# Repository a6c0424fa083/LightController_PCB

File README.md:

# LightController_PCB
This is the PCB (designed in KiCad) used in the LightController software

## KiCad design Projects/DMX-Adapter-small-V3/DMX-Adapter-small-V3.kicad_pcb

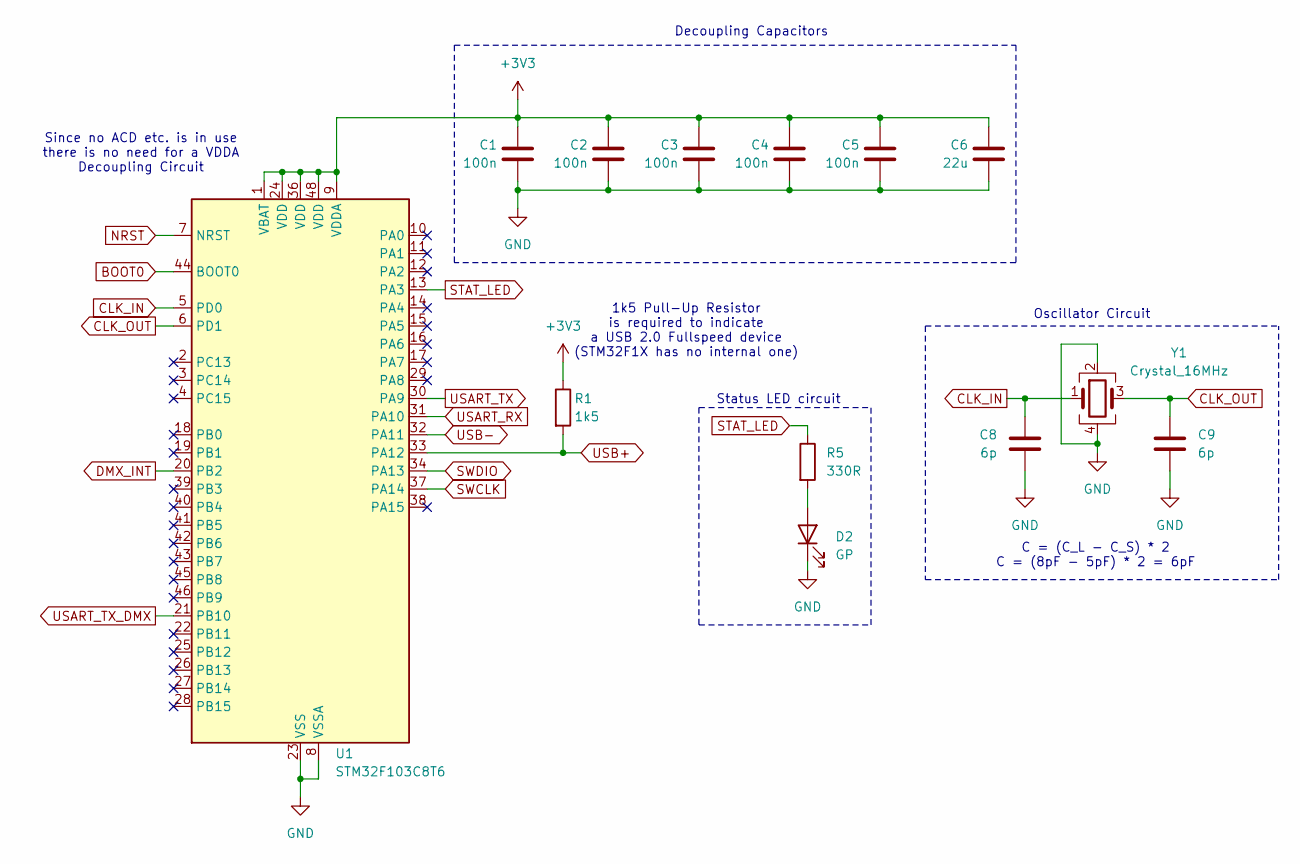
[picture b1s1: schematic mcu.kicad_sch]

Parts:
C1, C2, C3, C4, C5: 100n; C_0402_1005Metric; Mouser-Nr 81-GRM152D70G104ME5D
C6: 22u; C_0603_1608Metric; Mouser-Nr 81-GRM188C80J226ME5D
C8, C9: 6p; C_0402_1005Metric; Mouser-Nr 81-GCQ1555C1H6R0BB1D
D2: GP; D_0603_1608Metric; Mouser-Nr 755-SML-D12V8WT86
R1: 1k5; R_0402_1005Metric; Mouser-Nr 667-ERA-2VEB1501X
R5: 330R; R_0402_1005Metric; Mouser-Nr 71-CRCW0402330RFKEDH
U1: STM32F103C8T6; LQFP-48_7x7mm_P0.5mm; Mouser-Nr 511-STM32F103C8T6
Y1: Crystal_16MHz; Crystal_Wuerth_830108207109; Mouser-Nr 710-830108207109

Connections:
+3V3: C1.1, C2.1, C3.1, C4.1, C5.1, C6.1, R1.1, U1.1 (VBAT), U1.9 (VDDA), U1.24 (VDD), U1.36 (VDD), U1.48 (VDD); also elsewhere on the board
BOOT0: U1.44 (BOOT0); also elsewhere on the board
CLK_IN: C8.1, U1.5 (PD0), Y1.1
CLK_OUT: C9.1, U1.6 (PD1), Y1.3
DMX_INT: U1.20 (PB2); also elsewhere on the board
GND: C1.2, C2.2, C3.2, C4.2, C5.2, C6.2, C8.2, C9.2, D2.1 (K), U1.8 (VSSA), U1.23 (VSS), U1.35 (VSS), U1.47 (VSS), Y1.2, Y1.4; also elsewhere on the board
NRST: U1.7 (NRST); also elsewhere on the board
unnamed: D2.2 (A), R5.2
STAT_LED: R5.1, U1.13 (PA3)
SWCLK: U1.37 (PA14); also elsewhere on the board
SWDIO: U1.34 (PA13); also elsewhere on the board
USART_RX: U1.31 (PA10); also elsewhere on the board
USART_TX: U1.30 (PA9); also elsewhere on the board
USART_TX_DMX: U1.21 (PB10); also elsewhere on the board
USB+: R1.2, U1.33 (PA12); also elsewhere on the board
USB-: U1.32 (PA11); also elsewhere on the board

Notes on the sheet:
Status LED circuit
1k5 Pull-Up Resistor is required to indicate a USB 2.0 Fullspeed device (STM32F1X has no internal one)
Oscillator Circuit
Decoupling Capacitors
C = (C_L - C_S) * 2 C = (8pF - 5pF) * 2 = 6pF
Since no ACD etc. is in use there is no need for a VDDA Decoupling Circuit

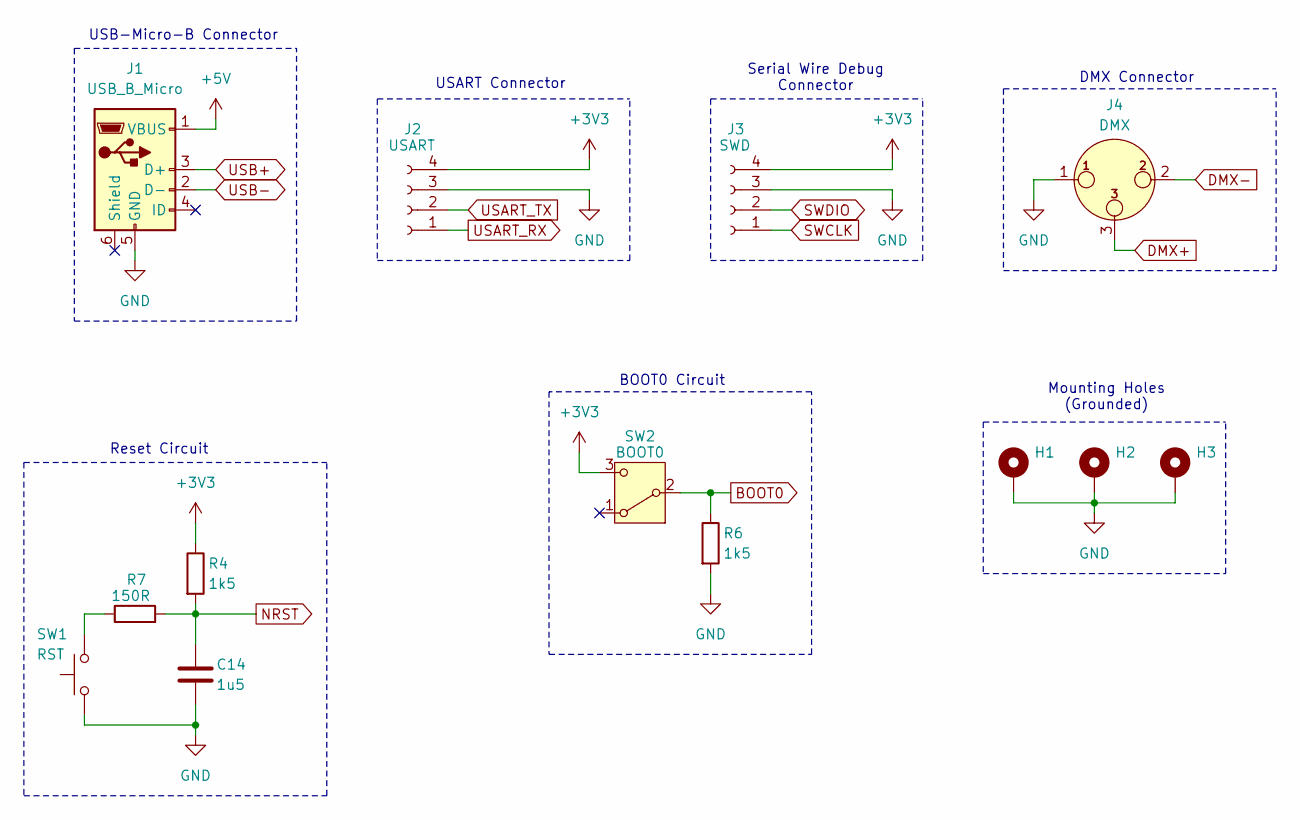
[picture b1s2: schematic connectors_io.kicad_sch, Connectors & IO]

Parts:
C14: 1u5; C_0603_1608Metric; Mouser-Nr 810-C1608X8L0J155K08
H1, H2, H3: MountingHole_Pad; MountingHole_2.2mm_M2_Pad
J1: USB_B_Micro; USB_Micro-B_Wuerth_629105150521; Mouser-Nr 710-629105150521
J2: USART; PinSocket_1x04_P2.54mm_Vertical; Mouser-Nr 710-61300411821
J3: SWD; PinSocket_1x04_P2.54mm_Vertical; Mouser-Nr 710-61300411821
J4: DMX; XLR3_Female; Mouser-Nr 568-NC3FAAH-1
R4, R6: 1k5; R_0402_1005Metric; Mouser-Nr 667-ERA-2VEB1501X
R7: 150R; R_0402_1005Metric; Mouser-Nr 660-SG73P1EWTTP151J
SW1: RST; omron_B3U-1000P; Mouser-Nr 653-B3U-1000P
SW2: BOOT0; wuerth_slide_switch_450404015514; Mouser-Nr 710-450404015514

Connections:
+3V3: J2.4, J3.4, R4.1, SW2.3 (C); also elsewhere on the board
+5V: J1.1 (VBUS); also elsewhere on the board
BOOT0: R6.1, SW2.2 (B); also elsewhere on the board
DMX+: J4.3; also elsewhere on the board
DMX-: J4.2; also elsewhere on the board
GND: C14.2, H1.1, H2.1, H3.1, J1.5 (GND), J2.3, J3.3, J4.1, R6.2, SW1.1; also elsewhere on the board
NRST: C14.1, R4.2, R7.2; also elsewhere on the board
unnamed: R7.1, SW1.2
SWCLK: J3.1; also elsewhere on the board
SWDIO: J3.2; also elsewhere on the board
USART_RX: J2.1; also elsewhere on the board
USART_TX: J2.2; also elsewhere on the board
USB+: J1.3 (D+); also elsewhere on the board
USB-: J1.2 (D-); also elsewhere on the board

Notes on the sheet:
Reset Circuit
USART Connector
USB-Micro-B Connector
Serial Wire Debug Connector
Mounting Holes (Grounded)
DMX Connector
BOOT0 Circuit

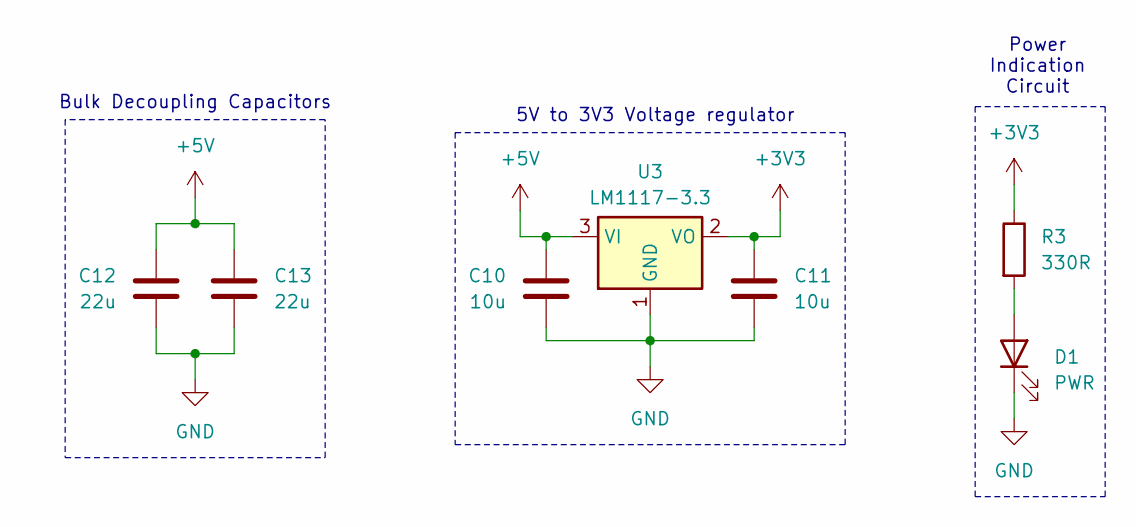
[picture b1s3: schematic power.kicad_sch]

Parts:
C10, C11: 10u; C_0805_2012Metric; Mouser-Nr 581-TACR106M006RTA
C12, C13: 22u; C_0603_1608Metric; Mouser-Nr 81-GRM188C80J226ME5D
D1: PWR; D_0603_1608Metric; Mouser-Nr 755-SML-D12V8WT86
R3: 330R; R_0402_1005Metric; Mouser-Nr 71-CRCW0402330RFKEDH
U3: LM1117-3.3; SOT-223-3_TabPin2; Mouser-Nr 926-LM1117IMPX33NOPB

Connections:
+3V3: C11.1, R3.1, U3.2 (VO); also elsewhere on the board
+5V: C10.1, C12.1, C13.1, U3.3 (VI); also elsewhere on the board
GND: C10.2, C11.2, C12.2, C13.2, D1.1 (K), U3.1 (GND); also elsewhere on the board
unnamed: D1.2 (A), R3.2

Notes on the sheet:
Power Indication Circuit
5V to 3V3 Voltage regulator
Bulk Decoupling Capacitors

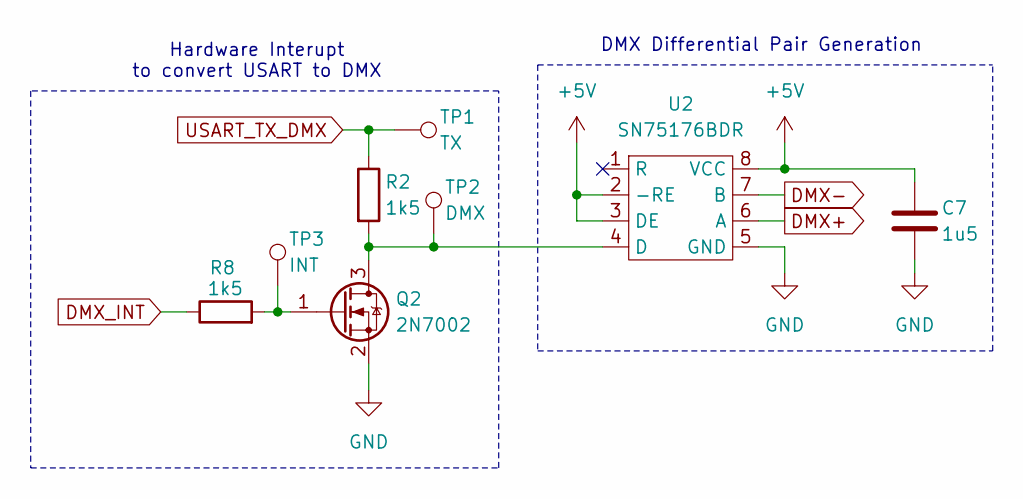
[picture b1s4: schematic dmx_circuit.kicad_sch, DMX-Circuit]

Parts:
C7: 1u5; C_0603_1608Metric; Mouser-Nr 810-C1608X8L0J155K08
Q2: 2N7002; SOT-23-3; Mouser-Nr 512-2N7002
R2, R8: 1k5; R_0402_1005Metric; Mouser-Nr 667-ERA-2VEB1501X
TP1: TX; TestPoint_Pad_D1.0mm
TP2: DMX; TestPoint_Pad_D1.0mm
TP3: INT; TestPoint_Pad_D1.0mm
U2: SN75176BDR; SN75176B-SOIC-8; Mouser-Nr 595-SN75176BDR

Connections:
+5V: C7.1, U2.2 (-RE), U2.3 (DE), U2.8 (VCC); also elsewhere on the board
DMX+: U2.6 (A); also elsewhere on the board
DMX-: U2.7 (B); also elsewhere on the board
DMX_INT: R8.1; also elsewhere on the board
GND: C7.2, Q2.2 (S), U2.5 (GND); also elsewhere on the board
unnamed: Q2.3 (D), R2.2, TP2.1, U2.4 (D)
unnamed: Q2.1 (G), R8.2, TP3.1
USART_TX_DMX: R2.1, TP1.1; also elsewhere on the board

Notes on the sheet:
DMX Differential Pair Generation
Hardware Interupt to convert USART to DMX

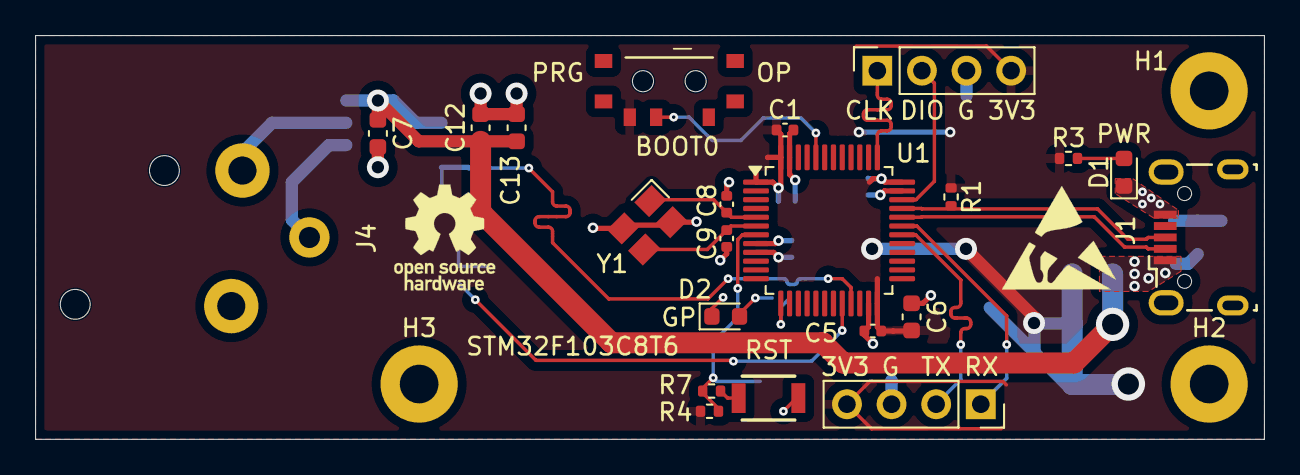
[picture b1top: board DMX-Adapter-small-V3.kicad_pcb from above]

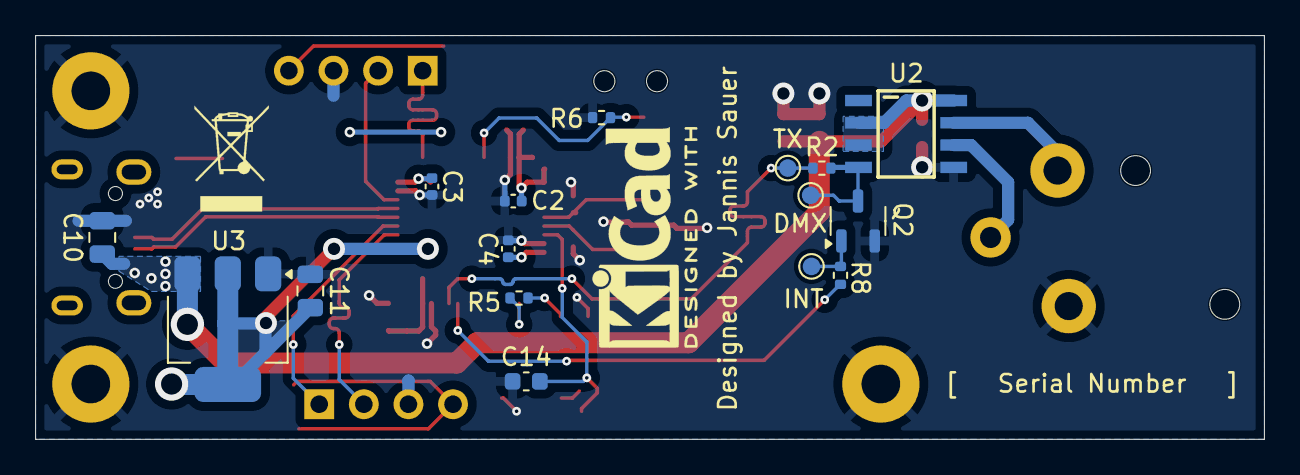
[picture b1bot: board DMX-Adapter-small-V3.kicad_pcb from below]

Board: 2 copper layers, 70.0 x 23.0 mm, 41 parts (16 on the bottom side), 23 nets.

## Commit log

2025-03-24 preliminary final version
2025-03-28 final
